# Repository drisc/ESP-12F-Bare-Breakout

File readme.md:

# ESP-12F Bare Breakout

This PCB breaks out the pins of ESP-12E/ESP-12F packages.
There are no resistors or circuitry to pull the 'Enable' pin HIGH or put the chips into flashing mode, it is just a breakout to make working with the chips easier so that you can build those circuits yourself.

I've included the library for the footprint of the ESP-12 under the libraries folder, to use it outside of this project look for 'ESP12E-SMD' in the library manager. Both the 'E' and 'F' board varients have the same pin layout.

## PCB Layout
![alt text][pcb]

[pcb]: https://github.com/drisc/ESP-12F-Bare-Breakout/raw/master/images/pcb.png "The PCB layout"

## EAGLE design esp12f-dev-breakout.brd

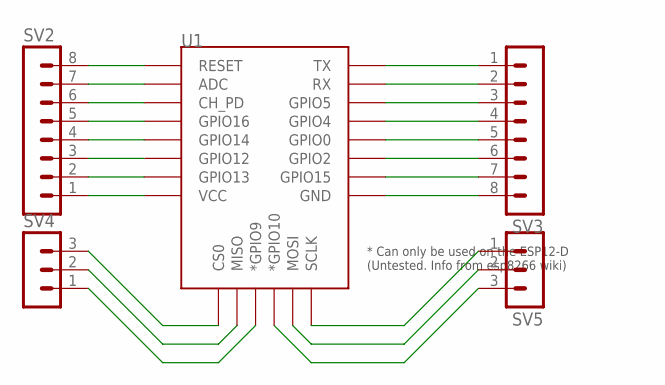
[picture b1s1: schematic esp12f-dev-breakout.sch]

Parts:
SV2, SV3: MA08-1
SV4, SV5: MA03-1
U1: ESP12ESMD; ESP12E-SMD

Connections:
unnamed: SV2.8, U1.RESET
unnamed: SV2.7, U1.ADC
unnamed: SV2.6, U1.CH_PD
unnamed: SV2.4, U1.GPIO14
unnamed: SV2.3, U1.GPIO12
unnamed: SV2.2, U1.GPIO13
unnamed: SV2.1, U1.VCC
unnamed: SV2.5, U1.GPIO16
unnamed: SV3.1, U1.TXD0 (TX)
unnamed: SV3.2, U1.RXD0 (RX)
unnamed: SV3.3, U1.GPIO5
unnamed: SV3.4, U1.GPIO4
unnamed: SV3.5, U1.GPIO0
unnamed: SV3.6, U1.GPIO2
unnamed: SV3.7, U1.GPIO15
unnamed: SV3.8, U1.GND
unnamed: SV4.3, U1.CS0
unnamed: SV4.2, U1.MISO
unnamed: SV4.1, U1.GPIO9 (*GPIO9)
unnamed: SV5.1, U1.SCLK
unnamed: SV5.2, U1.MOSI
unnamed: SV5.3, U1.GPIO10 (*GPIO10)

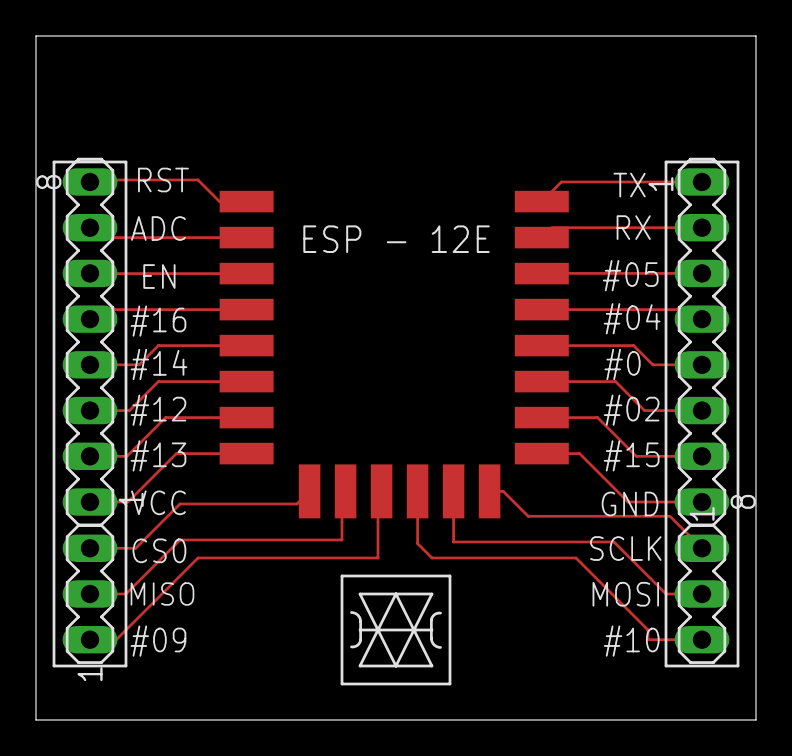
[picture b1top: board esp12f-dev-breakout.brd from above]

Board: 2 copper layers, 40.0 x 38.0 mm, 5 parts (0 on the bottom side), 22 nets.

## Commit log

2019-06-23 Added image, updated board file
